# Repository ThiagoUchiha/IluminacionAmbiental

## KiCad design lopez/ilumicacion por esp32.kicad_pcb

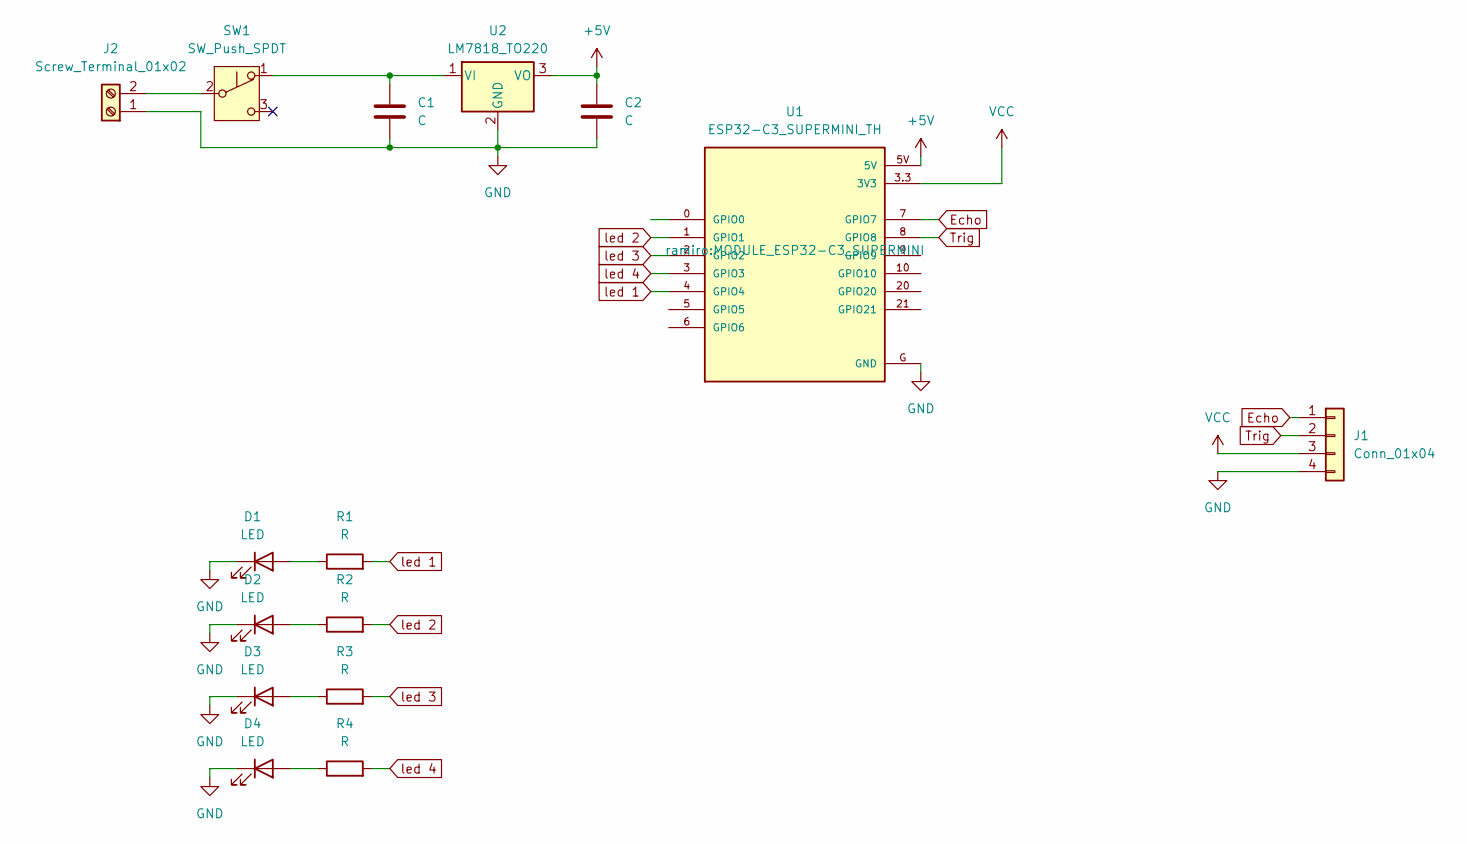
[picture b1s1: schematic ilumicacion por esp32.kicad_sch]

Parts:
C1, C2: C; C_1206_3216Metric
D1, D2, D3, D4: LED; LED_D4.0mm
J1: Conn_01x04; PinHeader_1x04_P1.00mm_Vertical
J2: Screw_Terminal_01x02; TerminalBlock_MaiXu_MX126-5.0-02P_1x02_P5.00mm
R1, R2, R3, R4: R; R_Axial_DIN0204_L3.6mm_D1.6mm_P7.62mm_Horizontal
SW1: SW_Push_SPDT; Pin_Header_3
U1: ESP32-C3_SUPERMINI_TH; MODULE_ESP32-C3_SUPERMINI
U2: LM7818_TO220; TO-220-3_Vertical

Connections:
+5V: C2.1, U1.5V, U2.3 (VO)
Echo: J1.1, U1.7 (GPIO7)
GND: C1.2, C2.2, D1.1 (K), D2.1 (K), D3.1 (K), D4.1 (K), J1.4, J2.1, U1.G (GND), U2.2 (GND)
unnamed: D1.2 (A), R1.1
unnamed: D2.2 (A), R2.1
unnamed: D3.2 (A), R3.1
unnamed: D4.2 (A), R4.1
unnamed: J2.2, SW1.2 (B)
unnamed: C1.1, SW1.1 (A), U2.1 (VI)
Trig: J1.2, U1.8 (GPIO8)
VCC: J1.3, U1.3.3 (3V3)
led 1: R1.2, U1.4 (GPIO4)
led 2: R2.2, U1.1 (GPIO1)
led 3: R3.2, U1.2 (GPIO2)
led 4: R4.2, U1.3 (GPIO3)

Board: 2 copper layers, 15 parts (2 on the bottom side), 15 nets, no tracks yet.
